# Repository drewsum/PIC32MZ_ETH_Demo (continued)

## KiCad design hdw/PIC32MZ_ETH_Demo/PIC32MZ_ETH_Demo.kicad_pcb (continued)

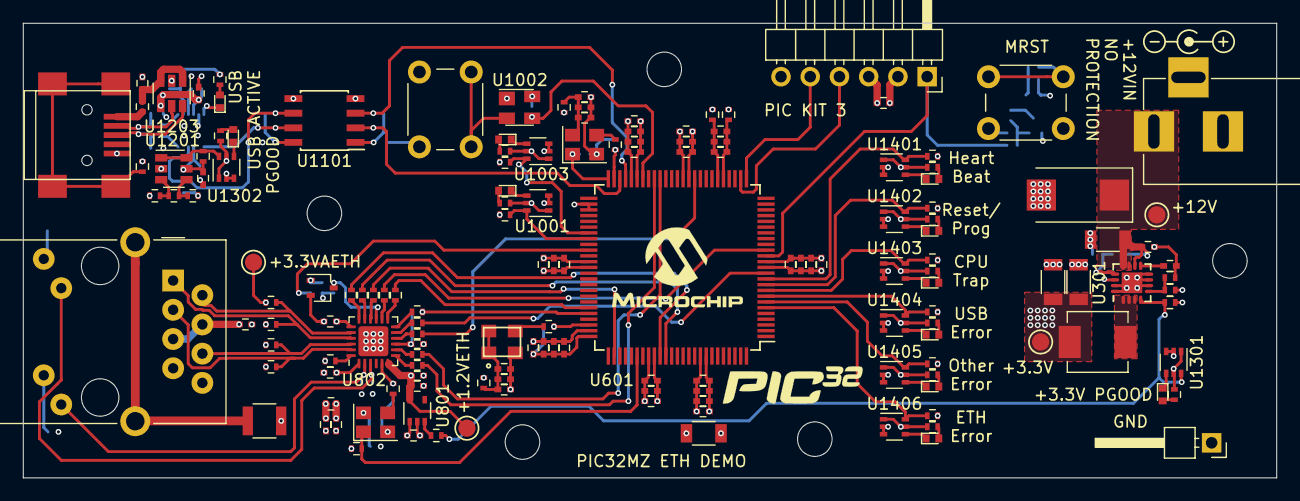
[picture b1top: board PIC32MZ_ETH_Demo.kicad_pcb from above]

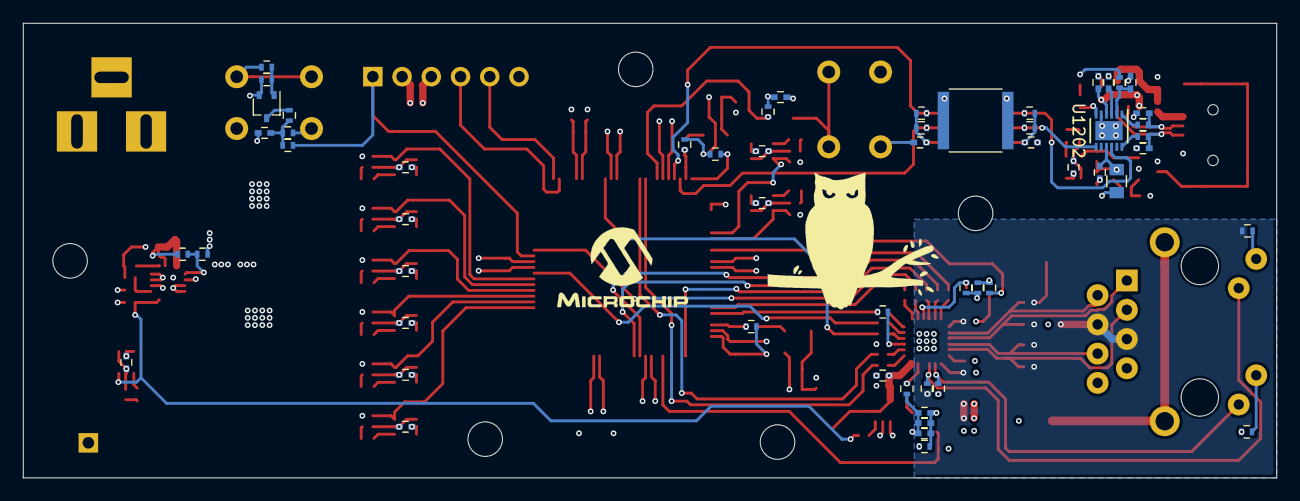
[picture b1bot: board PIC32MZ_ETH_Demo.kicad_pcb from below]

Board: 4 copper layers, 108.9 x 39.5 mm, 214 parts (56 on the bottom side), 114 nets.

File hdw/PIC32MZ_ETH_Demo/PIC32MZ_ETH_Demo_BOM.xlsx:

Qty | Reference(s) | Value | Digi-Key PN
1 | C201 | 100uF | 718-1102-1-ND
1 | C301 | 10uF | 1276-7031-1-ND
15 | C302, C505, C506, C512, C513, C519, C520, C526, C527, C703, C704, C803, C808, C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 | 10nF | 490-13295-1-ND
34 | C303, C401, C402, C502, C503, C509, C510, C516, C517, C523, C524, C701, C702, C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 | 0.1uF | 490-10701-1-ND
3 | C304, C305, C501 | 22uF | 1276-3148-1-ND
8 | C504, C511, C518, C525, C801, C804, C806, C807 | 10uF | 490-13211-1-ND
11 | C507, C508, C514, C515, C521, C522, C528, C529, C705, C706, C805 | 1nF | 399-1032-1-ND
1 | C809 | 1uF | 490-9665-1-ND
1 | C812 | 470pF | 399-1025-1-ND
1 | C901 | 0.022uF | 311-3793-1-ND
1 | C1102 | 0.56uF | 565-4707-1-ND
1 | C1205 | 4.7uF | 1276-2972-1-ND
2 | C1208, C1209 | 47pF | 399-17558-1-ND
5 | D1001, D1002, D1301, D1302, D1401 | Green | 1497-1219-1-ND
1 | D1201 | Yellow | 1497-1389-1-ND
5 | D1402, D1403, D1404, D1405, D1406 | Red | 1497-1174-1-ND
1 | J901 | RJ45_Amphenol_RJMG1BD3B8K1ANR | RJMG1BD3B8K1ANR-ND
1 | J1201 | USB_B_Mini | 732-2109-1-ND
1 | L301 | 2.2u | 541-1236-1-ND
8 | L501, L502, L701, L702, L801, L802, L1201, L1202 | 600R 0.5A | 490-5441-1-ND
8 | MK1501, MK1502, MK1505, MK1506, MK1509, MK1510, MK1513, MK1514 | Standoff | 1772-2080-ND
8 | MK1503, MK1504, MK1507, MK1508, MK1511, MK1512, MK1515, MK1516 | Screw | 36-9900-ND
2 | Q401, Q801 | BSS214NW | BSS214NWH6327XTSA1CT-ND
28 | R301, R302, R402, R404, R701, R704, R705, R802, R803, R804, R806, R819, R820, R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 | 10k | RMCF0402FT10K0CT-ND
13 | R303, R405, R1002, R1004, R1208, R1301, R1302, R1402, R1405, R1406, R1409, R141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 | 1k | 541-1.00KLCT-ND
12 | R304, R401, R801, R808, R809, R810, R811, R812, R813, R814, R815, R816 | 10 | 541-3964-1-ND
1 | R305 | 562k | 541-562KLCT-ND
1 | R306 | 180k | 541-180KLCT-ND
5 | R403, R702, R703, R805, R817 | 100 | 541-100LCT-ND
1 | R807 | 1.5k | 541-1.50KLCT-ND
1 | R818 | 12.1k | 541-CRCW040212K1FKTDCT-ND
4 | R901, R902, R903, R904 | 49.9 | 541-3967-1-ND
2 | R905, R906 | 332 | 541-332LCT-ND
1 | R907 | 0 | RMCF1210ZT0R00CT-ND
1 | R1202 | 487k | RMCF0402FT487KCT-ND
1 | R1203 | 6.04k | 541-4067-1-ND
1 | R1204 | 40.2k | 541-4097-1-ND
2 | R1206, R1207 | 27 | 541-4082-1-ND
1 | SW401 | MRST
1 | SW1001 | GPIO_SW
1 | U301 | TPS62130 | 296-37878-1-ND
1 | U601 | PIC32MZ2048EFG100_IPT | PIC32MZ2048EFG100-I/PT-ND
1 | U801 | TLV70012 | 296-27438-1-ND
1 | U802 | LAN8720A | LAN8720A-CP-CT-ND
10 | U1001, U1003, U1301, U1302, U1401, U1402, U1403, U1404, U1405, U1406 | 74LVC1G97 | 296-15582-1-ND
1 | U1002 | MAX6816 | MAX6816EUS+TCT-ND
1 | U1101 | ISO7321C | 296-42102-1-ND
1 | U1201 | TLV6700 | 296-51696-1-ND
1 | U1202 | FT234XD | 768-1178-1-ND
1 | U1203 | TPD3S014DBVR | 296-38835-1-ND
1 | X701 | ASE-8.000MHz | 535-9558-1-ND
1 | X702 | ECS-327KE | XC1751CT-ND
1 | X801 | ASE-25.000MHz | 535-13429-1-ND

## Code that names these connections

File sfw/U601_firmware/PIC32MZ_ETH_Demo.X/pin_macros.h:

#ifndef _PIN_MACROS_H    /* Guard against multiple inclusion */
#define _PIN_MACROS_H


#include <xc.h>

#define HIGH    1
#define LOW     0

// These pin macros allow for easier manipulation of GPIO with matching
// signal names from the hardware schematic

// Port A
#define ETH_PHY_RESET_PIN       LATAbits.LATS3

// Port B
#define nGPIO_SW_PIN            PORTBbits.RB15

// Port C
#define ETH_ERROR_LED_PIN       LATCbits.LATC1
#define OTHER_ERROR_LED_PIN     LATCbits.LATC2
#define USB_ERROR_LED_PIN       LATCbits.LATC3
#define CPU_EXCEPTION_LED_PIN   LATCbits.LATC4
#define MCU_POSC_ENABLE_PIN     LATCbits.LATC15

// Port D

// Port E

// Port F
#define GPIO_LED_2_PIN          LATFbits.LATF2
#define GPIO_LED_1_PIN          LATFbits.LATF8

// Port G
#define RESET_LED_PIN           LATGbits.LATG6
#define HEARTBEAT_LED_PIN       LATGbits.LATG7


#endif /* _PIN_MACROS_H */

/* *****************************************************************************
 End of File
 */

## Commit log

2020-03-12 modified gitignore
2020-03-12 Added hardware project, started schematic
2020-03-29 More schematic tweaks, followed PHY design guide
2020-04-05 Populated digi-key pn's
2020-04-05 Started arranging parts on PCB
2020-04-06 Added BOM, finished arranging parts
2020-04-10 Finished board layout
2020-06-10 finished board
2020-06-10 Added MCU firmware project
2020-06-10 Added pin macros, device control, other early stuff
2020-06-10 added pin macros, gpio setup
2020-06-11 regenerated sch pdf, ported a ton of code
2020-06-11 more porting from older projects
2020-06-11 More porting
